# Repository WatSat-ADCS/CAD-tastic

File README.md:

# CAD-tastic

All the CAD files for ADCS. This will include the circuits for 
* sensor boards
* ADCS motherboard

We are using [KiCad] for this. There are several good [tutorials] available. For making libaries, we suggest [KiCAD quick library].

[KiCad]: http://www.kicad.org/display/KICAD/KiCad+EDA+Software+Suite
[tutorials]: http://www.kicad.org/display/KICAD/Tutorials
[KiCAD quick library]: http://kicad.rohrbacher.net/quicklib.php

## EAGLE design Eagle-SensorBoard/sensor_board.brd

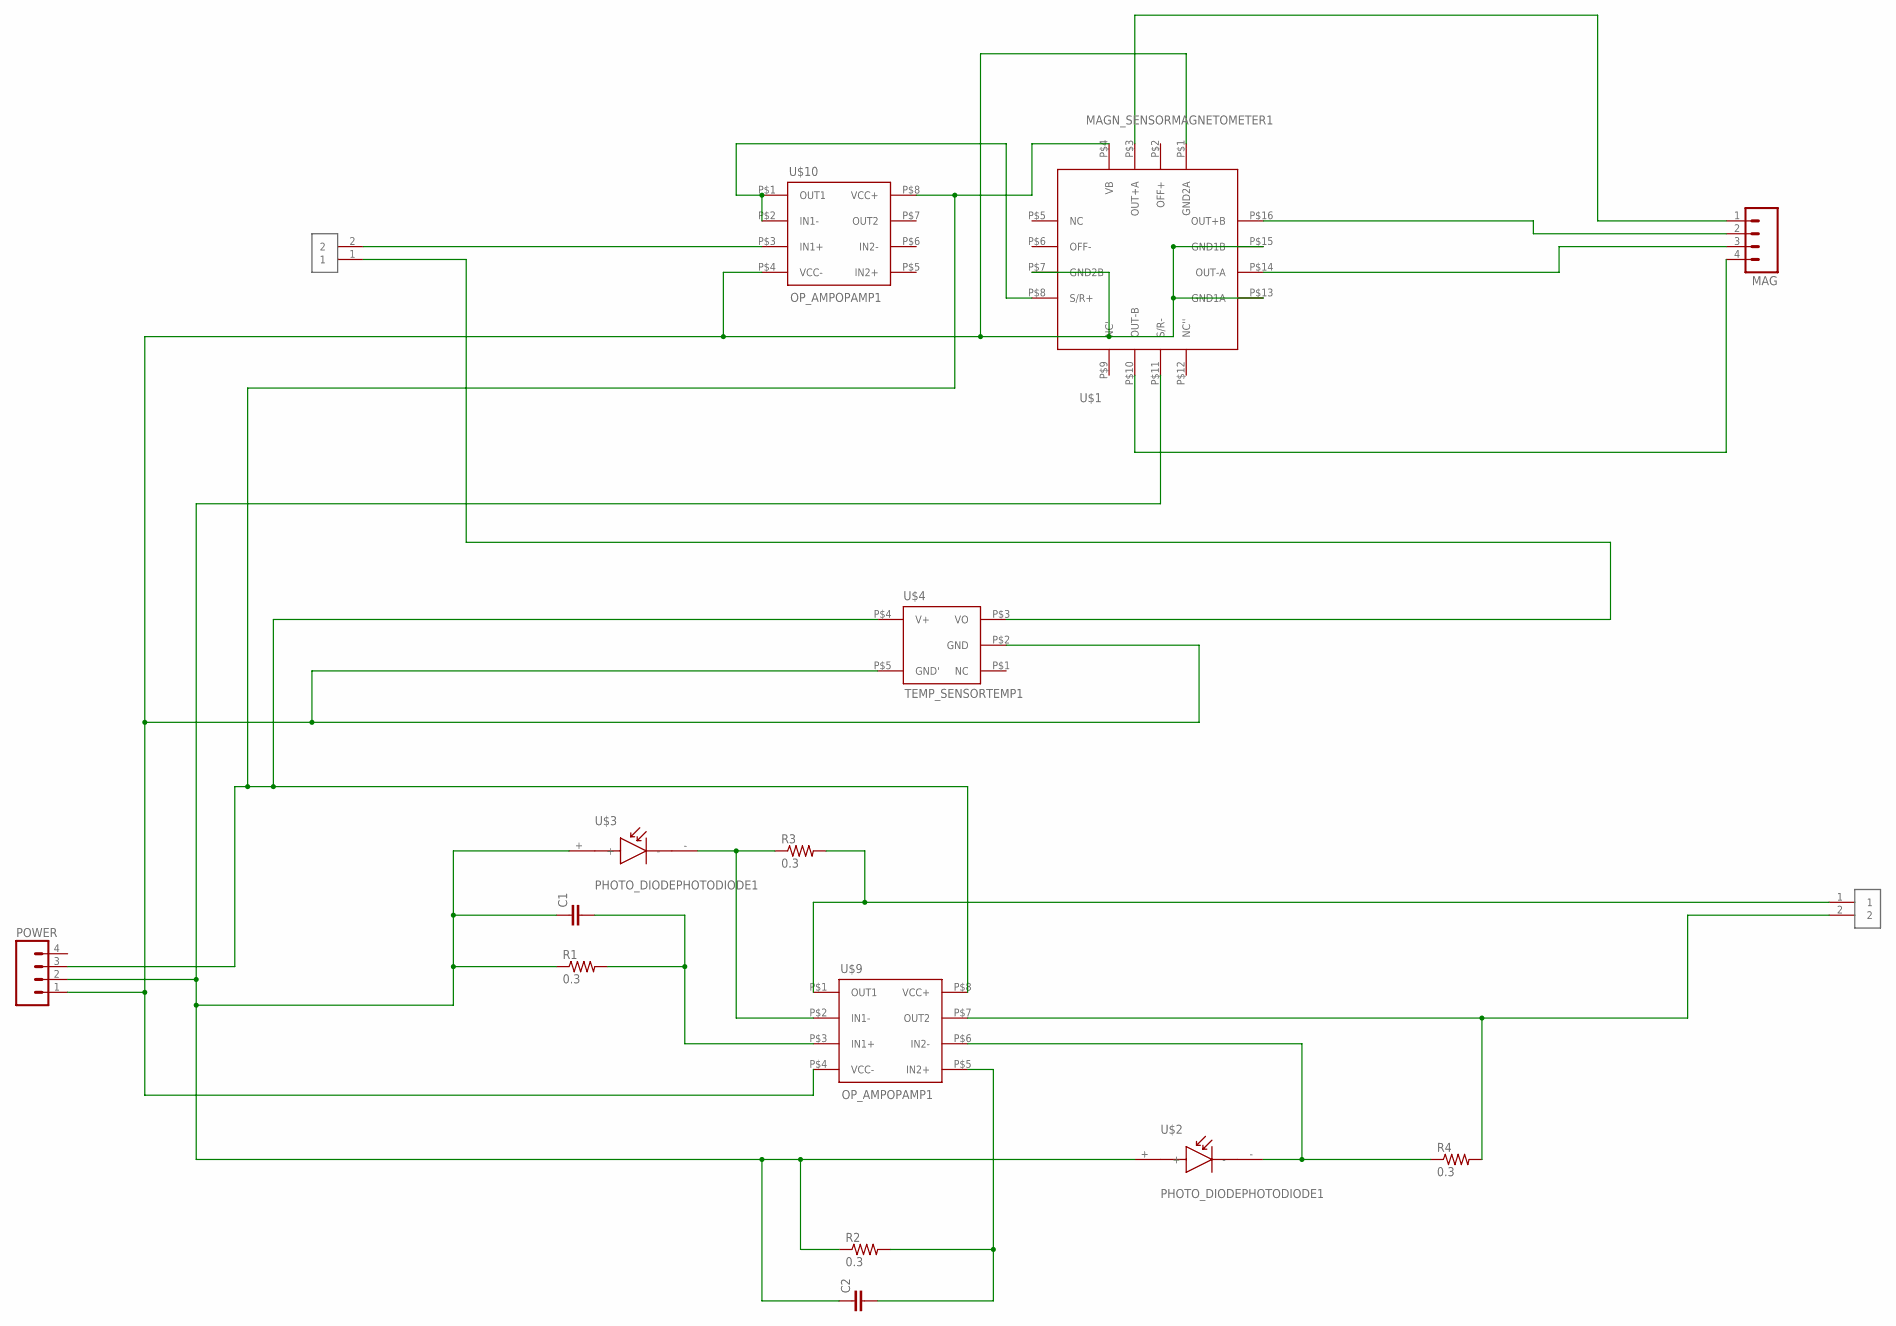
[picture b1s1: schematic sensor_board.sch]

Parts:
C1, C2: CAP0402-CAP; 0402-CAP
MAG: 1X04_HEADER"; 1X04_HEADER
MAGSR_TEMP: 1X02_HEADER
PHOTODIODE_OUT: 1X02_HEADER
POWER: 1X04_HEADER"; 1X04_HEADER
R1, R2, R3, R4: 0.3; 0805
U$1: MAGN_SENSORMAGNETOMETER1; MAGNETOMETER
U$2, U$3: PHOTO_DIODEPHOTODIODE1; PHOTODIODE
U$4: TEMP_SENSORTEMP1; TEMP
U$9, U$10: OP_AMPOPAMP1; OPAMP

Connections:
0V: POWER.1, U$1.P$1 (GND2A), U$1.P$7 (GND2B), U$1.P$13 (GND1A), U$1.P$15 (GND1B), U$4.P$2 (GND), U$4.P$5 (GND'), U$9.P$4 (VCC-), U$10.P$4 (VCC-)
2.5V: C1.1, C2.1, POWER.2, R1.1, R2.1, U$1.P$11 (S/R-), U$2.+, U$3.+
5V: POWER.3, U$1.P$4 (VB), U$4.P$4 (V+), U$9.P$8 (VCC+), U$10.P$8 (VCC+)
unnamed: C1.2, R1.2, U$9.P$3 (IN1+)
unnamed: R3.1, U$3.-, U$9.P$2 (IN1-)
unnamed: MAGSR_TEMP.2, U$10.P$3 (IN1+)
unnamed: U$1.P$8 (S/R+), U$10.P$1 (OUT1), U$10.P$2 (IN1-)
unnamed: C2.2, R2.2, U$9.P$5 (IN2+)
unnamed: R4.1, U$2.-, U$9.P$6 (IN2-)
unnamed: PHOTODIODE_OUT.2, R4.2, U$9.P$7 (OUT2)
unnamed: PHOTODIODE_OUT.1, R3.2, U$9.P$1 (OUT1)
unnamed: MAG.1, U$1.P$3 (OUT+A)
unnamed: MAGSR_TEMP.1, U$4.P$3 (VO)
unnamed: MAG.4, U$1.P$10 (OUT-B)
unnamed: MAG.3, U$1.P$14 (OUT-A)
unnamed: MAG.2, U$1.P$16 (OUT+B)

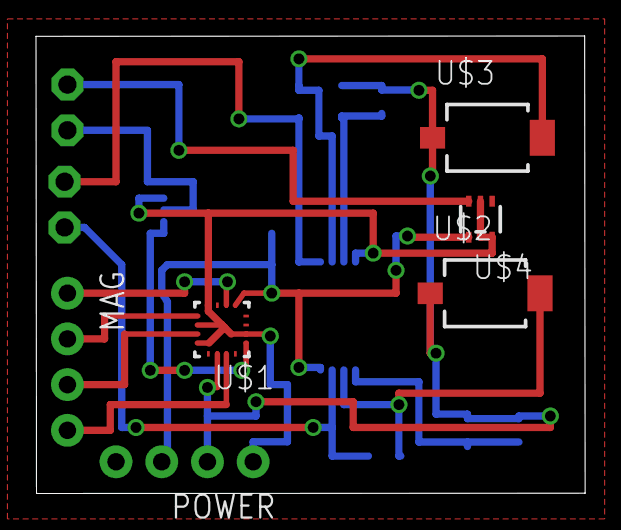
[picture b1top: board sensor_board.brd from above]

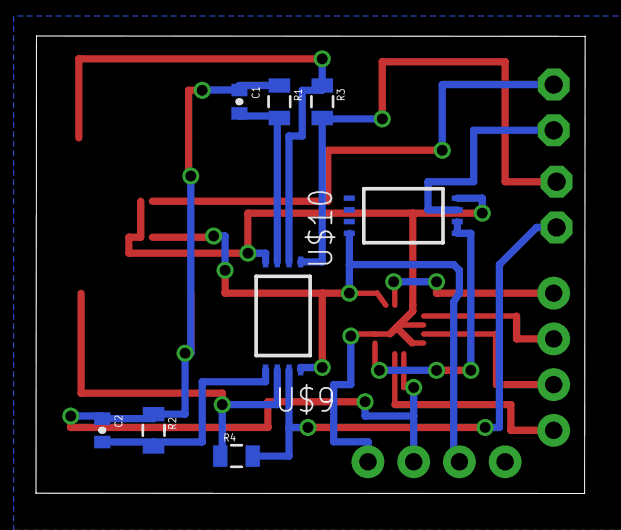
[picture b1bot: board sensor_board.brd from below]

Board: 2 copper layers, 30.5 x 25.4 mm, 16 parts (8 on the bottom side), 16 nets.

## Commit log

2015-04-01 add KiCad for an opamp circuit
    - this circuit should be used test v1 pcbs
2015-04-08 add lib files for HMC5883L (3-axis mag)
2015-04-09 add libs for mux
2015-04-09 add libs for temp. sensor
2015-04-09 add lib for photodiode
2015-04-09 update libs with new pins
2015-05-13 add libs for 2 axis magnetometer
    part number HMC1051
2015-05-13 Revert "add libs for 2 axis magnetometer"
    This reverts commit 53651d41479a995242046bff5ef0b3e577925ecc.
2015-05-13 rename files........
2015-05-13 make it work with KiCAD
2015-05-14 update HMC1051 lib
2015-05-16 make schematic for sensor board
2015-05-16 add label to everything on sensor board
2015-06-02 current state
2015-06-03 add readme and license
2015-09-17 moving a resistor to the wrong place.
    Please undo me!
2015-10-08 Add arduino boards from Eagle project
    This did not exist in any repo yet but should exist somewhere so that
    everyone on the team has access to it.
2015-11-05 Add eagle schematics for the sensor board
2016-09-22 Assortment of Layouts for the ADCS board
    This project contains the various components and the old arduino board
    that are put together on a new layout (arduinoNew)
2016-09-22 Data Sheets and Schematics
2021-11-10 Update README.md
    https://forum.kicad.info/t/warning-avoid-all-links-to-kicad-pcb-org-use-kicad-org/31521

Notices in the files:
parts and their libraries:
SparkFun-Resistors: Licensing: Creative Commons ShareAlike 4.0 International - https://creativecommons.org/licenses/by-sa/4.0
SparkFun: Licensing: CC v3.0 Share-Alike You are welcome to use this library for commercial purposes.
